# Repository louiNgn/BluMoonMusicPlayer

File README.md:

# BluMoon Music Player
## a scuffed MP3 player PCB with a scrolling rotary encoder!

## BOM
| Reference   | Qty | Value                     | DNP | Exclude from BOM | Exclude from Board | Footprint                                                      | Datasheet                                                           |
|-------------|-----|---------------------------|-----|------------------|--------------------|----------------------------------------------------------------|---------------------------------------------------------------------|
| BT1         | 1   | Battery                   |     |                  |                    | Connector_PinSocket_2.54mm:PinSocket_1x02_P2.54mm_Vertical     |                                                                     |
| J1          | 1   | Conn_01x04_Socket         |     |                  |                    | Display:ER_OLEDM0.91_1x-I2C                                    |                                                                     |
| J2          | 1   | Conn_01x04_Socket         |     |                  |                    | Connector_PinSocket_2.54mm:PinSocket_1x04_P2.54mm_Vertical     |                                                                     |
| J3          | 1   | AudioJack3                |     |                  |                    | Connector_Audio:Jack_3.5mm_CUI_SJ1-3533NG_Horizontal           |                                                                     |
| R1          | 1   | 1k                        |     |                  |                    | PCM_SparkFun-Resistor:R_0603_1608Metric                        | https://www.vishay.com/docs/20035/dcrcwe3.pdf                       |
| R2,R3       | 2   | 100k                      |     |                  |                    | PCM_SparkFun-Resistor:R_0603_1608Metric                        | https://www.vishay.com/docs/20035/dcrcwe3.pdf                       |
| SW1         | 1   | RotaryEncoder_Switch      |     |                  |                    | Keebio-Parts.pretty-master:RotaryEncoder_EC11B-Horizontal-Dual |                                                                     |
| SW2         | 1   | SPDT_Slide_PTH_11.6x4.0mm |     |                  |                    | PCM_SparkFun-Switch:Slide_SPDT_PTH_11.6x4.0mm                  | https://www.sparkfun.com/datasheets/Components/Buttons/P040040c.pdf |
| SW3,SW4,SW5 | 3   | SW_Push                   |     |                  |                    | Button_Switch_SMD:SW_Push_1P1T_NO_E-Switch_TL3301NxxxxxG       |                                                                     |
| U1          | 1   | ESP32-S3-SuperMini        |     |                  |                    | ESP-S3_SuperMini:ESP32-S3-SuperMini                            |                                                                     |
| U2          | 1   | DFR0299                   |     |                  |                    | DFPlayerMini:MODULE_DFR0299                                    |                                                                     |

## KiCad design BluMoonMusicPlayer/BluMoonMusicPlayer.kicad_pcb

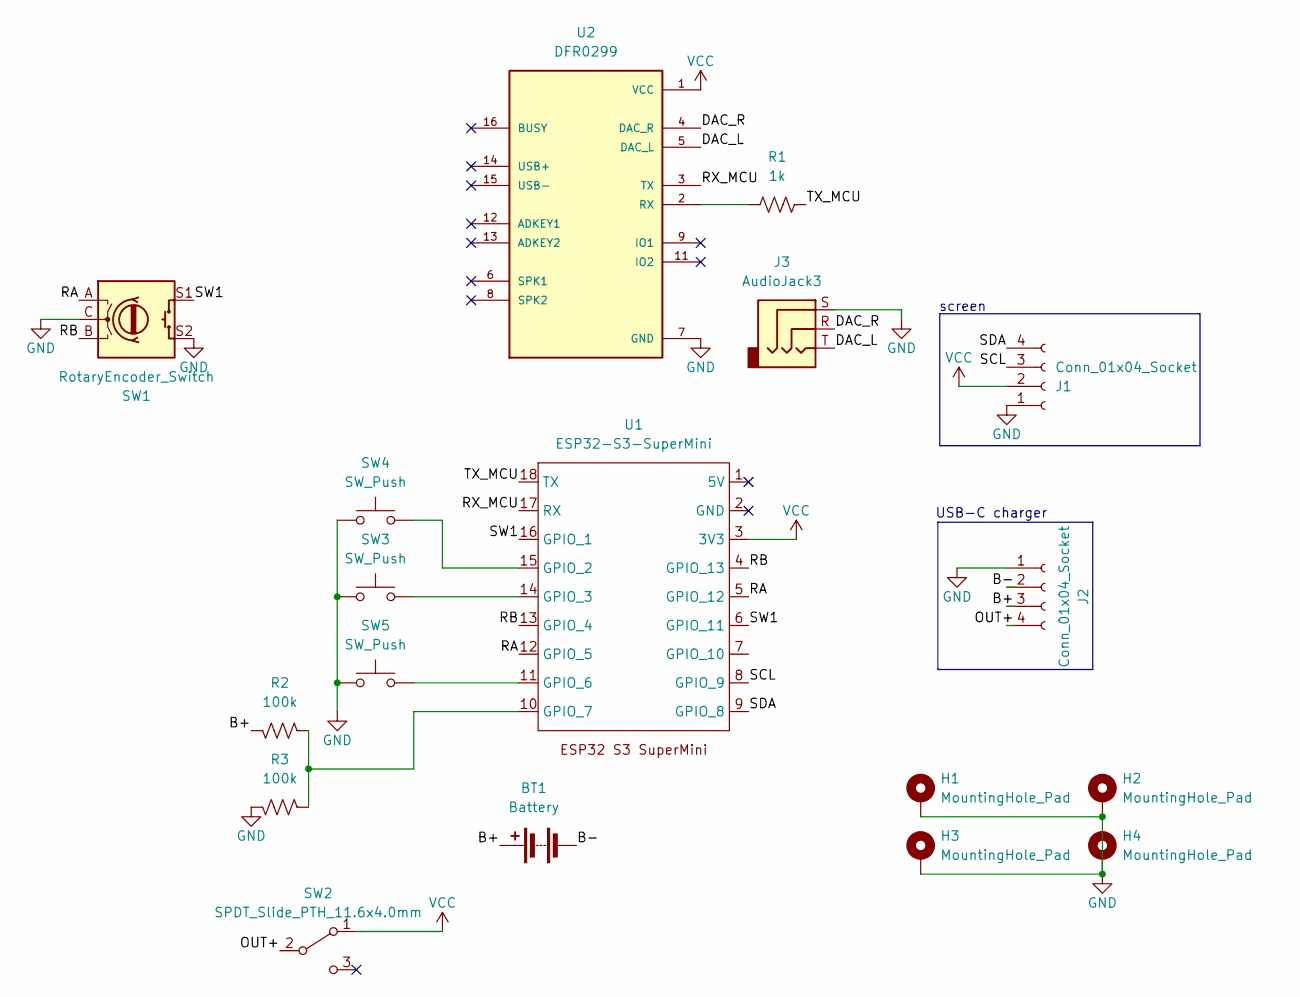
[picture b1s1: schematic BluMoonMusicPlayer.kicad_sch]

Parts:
BT1: Battery; PinSocket_1x02_P2.54mm_Vertical
H1, H2, H3, H4: MountingHole_Pad; MountingHole_2.2mm_M2_DIN965_Pad_TopBottom
J1: Conn_01x04_Socket; ER_OLEDM0.91_1x-I2C
J2: Conn_01x04_Socket; PinSocket_1x04_P2.54mm_Vertical
J3: AudioJack3; Jack_3.5mm_CUI_SJ1-3533NG_Horizontal
R1: 1k; R_0603_1608Metric
R2, R3: 100k; R_0603_1608Metric
SW1: RotaryEncoder_Switch; RotaryEncoder_EC11B-Horizontal-Dual
SW2: SPDT_Slide_PTH_11.6x4.0mm; Slide_SPDT_PTH_11.6x4.0mm
SW3, SW4, SW5: SW_Push; SW_Push_1P1T_NO_E-Switch_TL3301NxxxxxG
U1: ESP32-S3-SuperMini
U2: DFR0299; MODULE_DFR0299

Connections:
/B+: BT1.1 (+), J2.3, R2.1
/B-: BT1.2 (-), J2.2
/DAC_L: J3.T, U2.5 (DAC_L)
/DAC_R: J3.R, U2.4 (DAC_R)
/OUT+: J2.4, SW2.2 (B)
/RA: SW1.A, U1.5 (GPIO_12), U1.12 (GPIO_5)
/RB: SW1.B, U1.4 (GPIO_13), U1.13 (GPIO_4)
/RX_MCU: U1.17 (RX), U2.3 (TX)
/SCL: J1.3, U1.8 (GPIO_9)
/SDA: J1.4, U1.9 (GPIO_8)
/SW1: SW1.S1, U1.6 (GPIO_11), U1.16 (GPIO_1)
/TX_MCU: R1.1, U1.18 (TX)
GND: H1.1 (1_1), H2.1 (1_1), H3.1 (1_1), H4.1 (1_1), J1.1, J2.1, J3.S, R3.1, SW1.C, SW1.S2, SW3.1, SW4.1, SW5.1, U2.7 (GND), U2.10 (GND)
unnamed: SW4.2, U1.15 (GPIO_2)
unnamed: SW3.2, U1.14 (GPIO_3)
unnamed: SW5.2, U1.11 (GPIO_6)
unnamed: R2.2, R3.2, U1.10 (GPIO_7)
unnamed: R1.2, U2.2 (RX)
VCC: J1.2, SW2.1 (A), U1.3 (3V3), U2.1 (VCC)

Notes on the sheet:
USB-C charger
screen

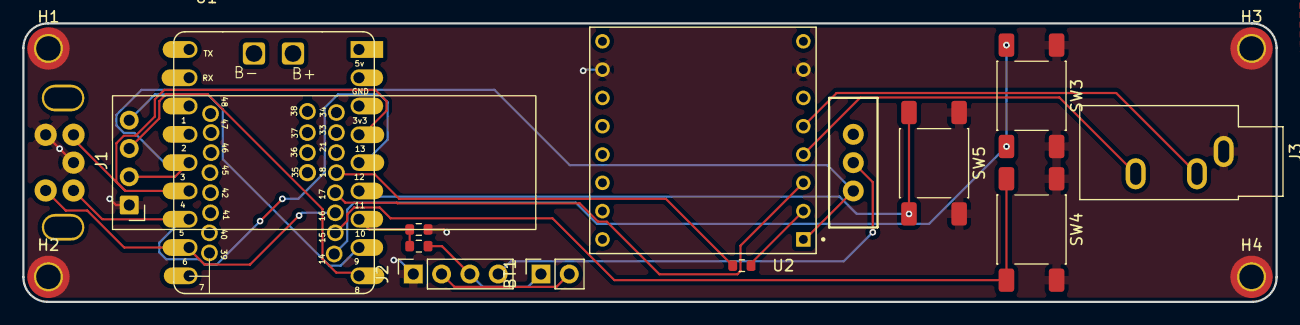
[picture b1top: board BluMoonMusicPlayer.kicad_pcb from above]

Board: 2 copper layers, 112.5 x 25.0 mm, 18 parts (0 on the bottom side), 19 nets.
